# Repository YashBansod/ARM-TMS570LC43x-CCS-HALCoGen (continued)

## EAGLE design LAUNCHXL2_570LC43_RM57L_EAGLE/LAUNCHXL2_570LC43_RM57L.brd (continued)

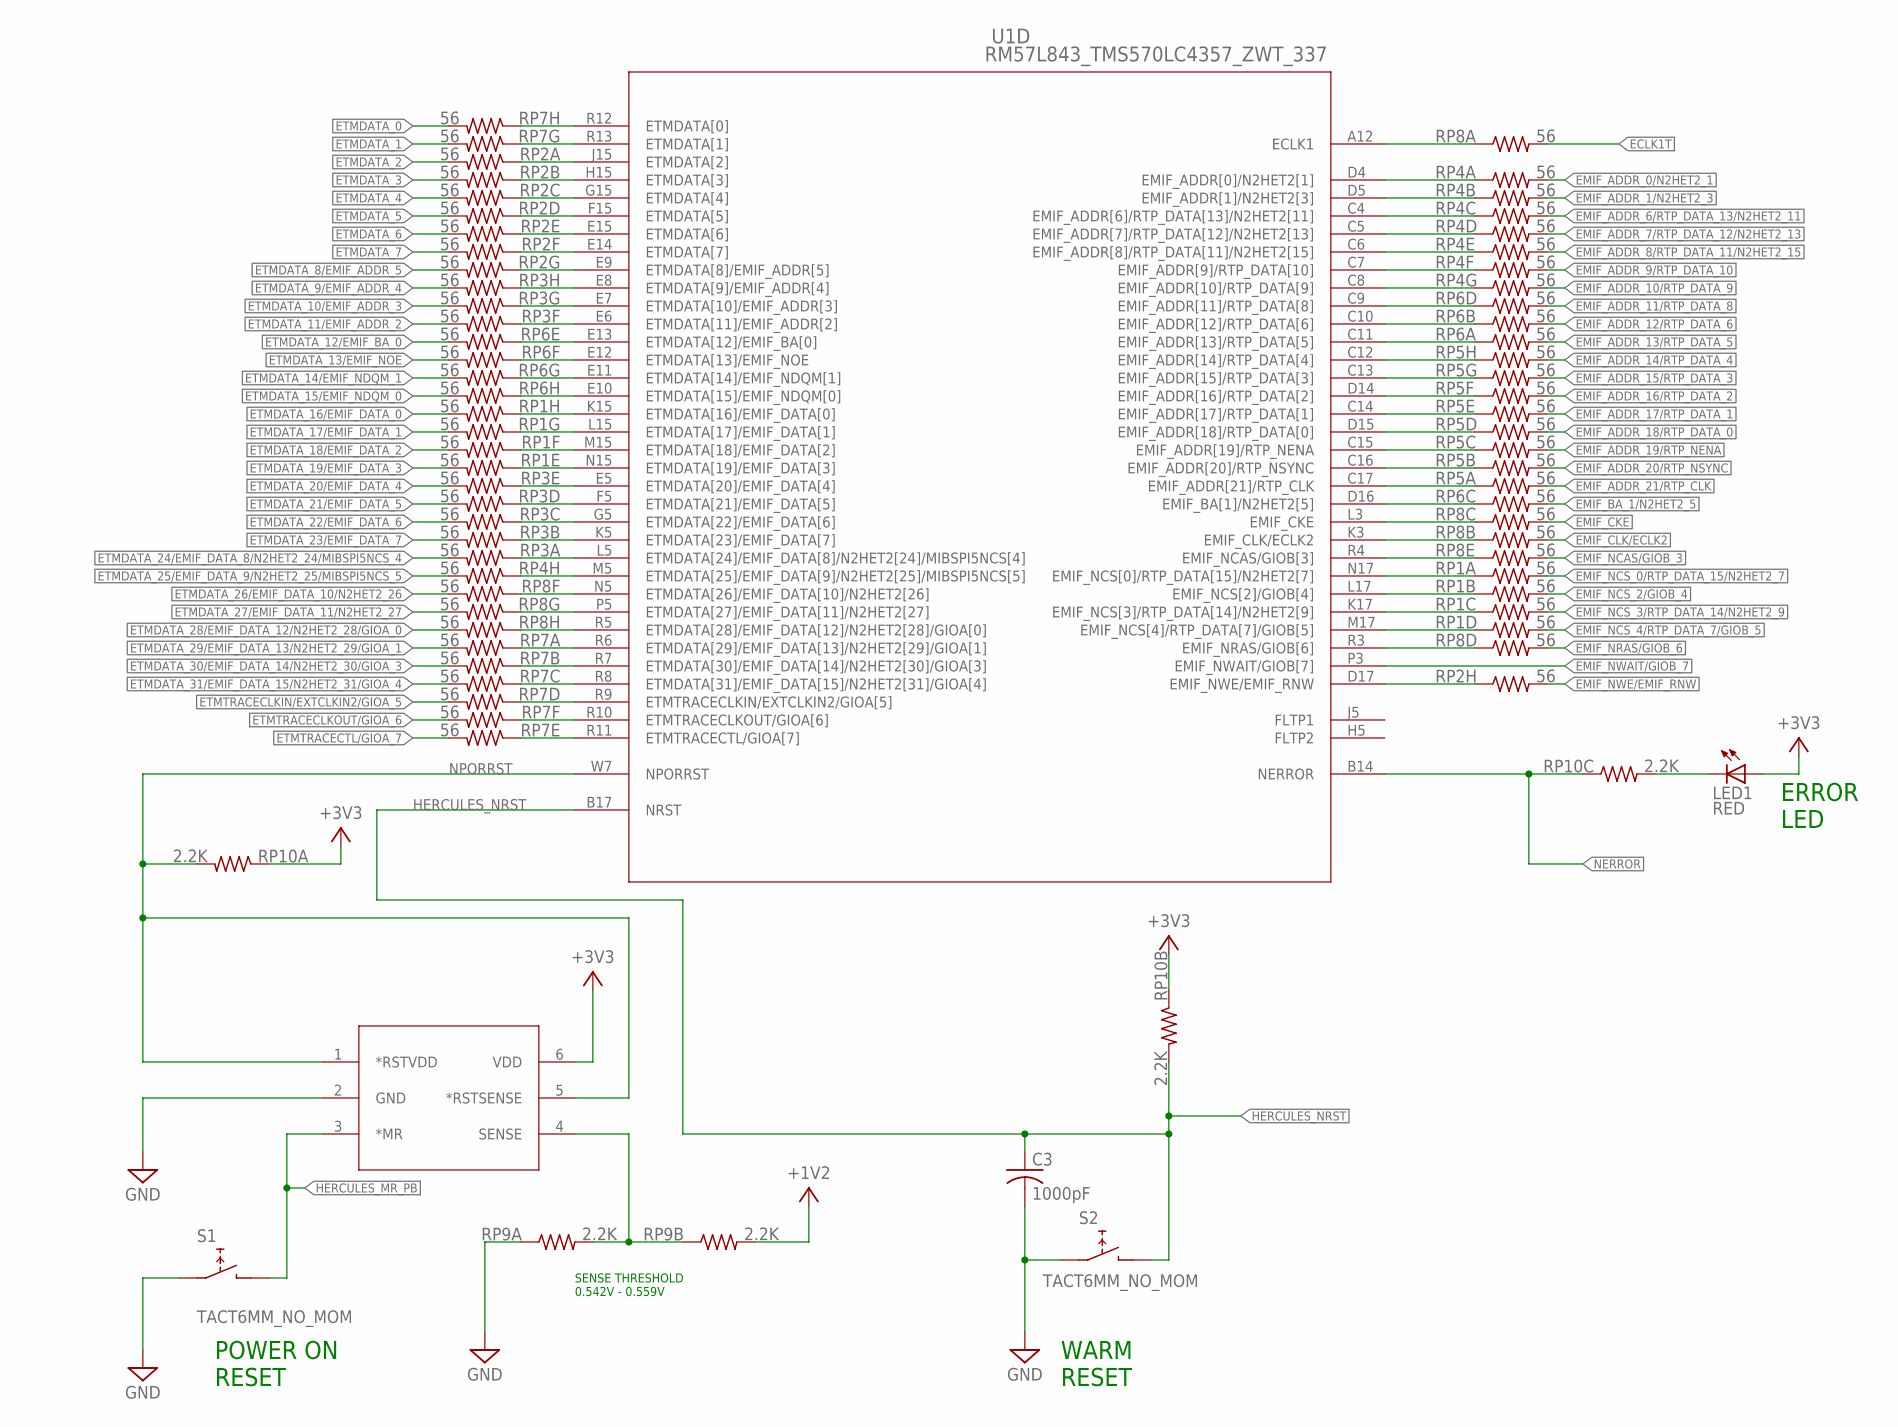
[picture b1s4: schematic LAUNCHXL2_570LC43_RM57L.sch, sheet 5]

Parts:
C3: 1000pF; C0201; PARTNO CC0201KRX7R8BB102
LED1: RED; CHIPLED_0603; PARTNO LS Q976-NR-1
RP1, RP2, RP3, RP4, RP5, RP6, RP7, RP8: 56; RP8_1506_1606; PARTNO MNR18E0APJ560
RP9, RP10: 2.2K; RP8_1506_1606; PARTNO MNR18E0APJ222
S1, S2: TACT6MM_NO_MOM; CK_PTS645_SMD; PARTNO PTS645SM43SMTR92 LFS
U1: RM57L843_TMS570LC4357_ZWT_337; ZWT337; PARTNO TMP5704357AZWTQQ1
U2: TPS3106K33_DBV_6; DBV6; PARTNO TPS3106K33DBVR

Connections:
+1V2: RP9.4 (2); also elsewhere on the board
+3V3: LED1.A, RP10.1, RP10.3 (1), U2.6 (VDD); also elsewhere on the board
ECLK1: RP8.1, U1.A12 (ECLK1)
ECLK1T: RP8.2; also elsewhere on the board
EMA0: RP4.1, U1.D4 (EMIF_ADDR[0]/N2HET2[1])
EMA1: RP4.3 (1), U1.D5 (EMIF_ADDR[1]/N2HET2[3])
EMA6: RP4.5 (1), U1.C4 (EMIF_ADDR[6]/RTP_DATA[13]/N2HET2[11])
EMA7: RP4.7 (1), U1.C5 (EMIF_ADDR[7]/RTP_DATA[12]/N2HET2[13])
EMA8: RP4.9 (1), U1.C6 (EMIF_ADDR[8]/RTP_DATA[11]/N2HET2[15])
EMA9: RP4.11 (1), U1.C7 (EMIF_ADDR[9]/RTP_DATA[10])
EMA10: RP4.13 (1), U1.C8 (EMIF_ADDR[10]/RTP_DATA[9])
EMA11: RP6.7 (1), U1.C9 (EMIF_ADDR[11]/RTP_DATA[8])
EMA12: RP6.3 (1), U1.C10 (EMIF_ADDR[12]/RTP_DATA[6])
EMA13: RP6.1, U1.C11 (EMIF_ADDR[13]/RTP_DATA[5])
EMA14: RP5.15 (1), U1.C12 (EMIF_ADDR[14]/RTP_DATA[4])
EMA15: RP5.13 (1), U1.C13 (EMIF_ADDR[15]/RTP_DATA[3])
EMA16: RP5.11 (1), U1.D14 (EMIF_ADDR[16]/RTP_DATA[2])
EMA17: RP5.9 (1), U1.C14 (EMIF_ADDR[17]/RTP_DATA[1])
EMA18: RP5.7 (1), U1.D15 (EMIF_ADDR[18]/RTP_DATA[0])
EMA19: RP5.5 (1), U1.C15 (EMIF_ADDR[19]/RTP_NENA)
EMA20: RP5.3 (1), U1.C16 (EMIF_ADDR[20]/RTP_NSYNC)
EMA21: RP5.1, U1.C17 (EMIF_ADDR[21]/RTP_CLK)
EMBA1: RP6.5 (1), U1.D16 (EMIF_BA[1]/N2HET2[5])
EMCAS: RP8.9 (1), U1.R4 (EMIF_NCAS/GIOB[3])
EMCKE: RP8.5 (1), U1.L3 (EMIF_CKE)
EMCLK: RP8.3 (1), U1.K3 (EMIF_CLK/ECLK2)
EMCS0: RP1.1, U1.N17 (EMIF_NCS[0]/RTP_DATA[15]/N2HET2[7])
EMCS2: RP1.3 (1), U1.L17 (EMIF_NCS[2]/GIOB[4])
EMCS3: RP1.5 (1), U1.K17 (EMIF_NCS[3]/RTP_DATA[14]/N2HET2[9])
EMCS4: RP1.7 (1), U1.M17 (EMIF_NCS[4]/RTP_DATA[7]/GIOB[5])
EMIF_ADDR_0/N2HET2_1: RP4.2; also elsewhere on the board
EMIF_ADDR_1/N2HET2_3: RP4.4 (2); also elsewhere on the board
EMIF_ADDR_6/RTP_DATA_13/N2HET2_11: RP4.6 (2); also elsewhere on the board
EMIF_ADDR_7/RTP_DATA_12/N2HET2_13: RP4.8 (2); also elsewhere on the board
EMIF_ADDR_8/RTP_DATA_11/N2HET2_15: RP4.10 (2); also elsewhere on the board
EMIF_ADDR_9/RTP_DATA_10: RP4.12 (2); also elsewhere on the board
EMIF_ADDR_10/RTP_DATA_9: RP4.14 (2); also elsewhere on the board
EMIF_ADDR_11/RTP_DATA_8: RP6.8 (2); also elsewhere on the board
EMIF_ADDR_12/RTP_DATA_6: RP6.4 (2); also elsewhere on the board
EMIF_ADDR_13/RTP_DATA_5: RP6.2; also elsewhere on the board
EMIF_ADDR_14/RTP_DATA_4: RP5.16 (2); also elsewhere on the board
EMIF_ADDR_15/RTP_DATA_3: RP5.14 (2); also elsewhere on the board
EMIF_ADDR_16/RTP_DATA_2: RP5.12 (2); also elsewhere on the board
EMIF_ADDR_17/RTP_DATA_1: RP5.10 (2); also elsewhere on the board
EMIF_ADDR_18/RTP_DATA_0: RP5.8 (2); also elsewhere on the board
EMIF_ADDR_19/RTP_NENA: RP5.6 (2); also elsewhere on the board
EMIF_ADDR_20/RTP_NSYNC: RP5.4 (2); also elsewhere on the board
EMIF_ADDR_21/RTP_CLK: RP5.2; also elsewhere on the board
EMIF_BA_1/N2HET2_5: RP6.6 (2); also elsewhere on the board
EMIF_CKE: RP8.6 (2); also elsewhere on the board
EMIF_CLK/ECLK2: RP8.4 (2); also elsewhere on the board
EMIF_NCAS/GIOB_3: RP8.10 (2); also elsewhere on the board
EMIF_NCS_0/RTP_DATA_15/N2HET2_7: RP1.2; also elsewhere on the board
EMIF_NCS_2/GIOB_4: RP1.4 (2); also elsewhere on the board
EMIF_NCS_3/RTP_DATA_14/N2HET2_9: RP1.6 (2); also elsewhere on the board
EMIF_NCS_4/RTP_DATA_7/GIOB_5: RP1.8 (2); also elsewhere on the board
EMIF_NRAS/GIOB_6: RP8.8 (2); also elsewhere on the board
EMIF_NWAIT/GIOB_7: U1.P3 (EMIF_NWAIT/GIOB[7]); also elsewhere on the board
EMIF_NWE/EMIF_RNW: RP2.16 (2); also elsewhere on the board
EMRAS: RP8.7 (1), U1.R3 (EMIF_NRAS/GIOB[6])
EMWE: RP2.15 (1), U1.D17 (EMIF_NWE/EMIF_RNW)
ETD0: RP7.15 (1), U1.R12 (ETMDATA[0])
ETD1: RP7.13 (1), U1.R13 (ETMDATA[1])
ETD2: RP2.1, U1.J15 (ETMDATA[2])
ETD3: RP2.3 (1), U1.H15 (ETMDATA[3])
ETD4: RP2.5 (1), U1.G15 (ETMDATA[4])
ETD5: RP2.7 (1), U1.F15 (ETMDATA[5])
ETD6: RP2.9 (1), U1.E15 (ETMDATA[6])
ETD7: RP2.11 (1), U1.E14 (ETMDATA[7])
ETD8: RP2.13 (1), U1.E9 (ETMDATA[8]/EMIF_ADDR[5])
ETD9: RP3.15 (1), U1.E8 (ETMDATA[9]/EMIF_ADDR[4])
ETD10: RP3.13 (1), U1.E7 (ETMDATA[10]/EMIF_ADDR[3])
ETD11: RP3.11 (1), U1.E6 (ETMDATA[11]/EMIF_ADDR[2])
ETD12: RP6.9 (1), U1.E13 (ETMDATA[12]/EMIF_BA[0])
ETD13: RP6.11 (1), U1.E12 (ETMDATA[13]/EMIF_NOE)
ETD14: RP6.13 (1), U1.E11 (ETMDATA[14]/EMIF_NDQM[1])
ETD15: RP6.15 (1), U1.E10 (ETMDATA[15]/EMIF_NDQM[0])
ETD16: RP1.15 (1), U1.K15 (ETMDATA[16]/EMIF_DATA[0])
ETD17: RP1.13 (1), U1.L15 (ETMDATA[17]/EMIF_DATA[1])
ETD18: RP1.11 (1), U1.M15 (ETMDATA[18]/EMIF_DATA[2])
ETD19: RP1.9 (1), U1.N15 (ETMDATA[19]/EMIF_DATA[3])
ETD20: RP3.9 (1), U1.E5 (ETMDATA[20]/EMIF_DATA[4])
ETD21: RP3.7 (1), U1.F5 (ETMDATA[21]/EMIF_DATA[5])
ETD22: RP3.5 (1), U1.G5 (ETMDATA[22]/EMIF_DATA[6])
ETD23: RP3.3 (1), U1.K5 (ETMDATA[23]/EMIF_DATA[7])
ETD24: RP3.1, U1.L5 (ETMDATA[24]/EMIF_DATA[8]/N2HET2[24]/MIB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)
ETD25: RP4.15 (1), U1.M5 (ETMDATA[25]/EMIF_DATA[9]/N2HET2[25]/MIB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)
ETD26: RP8.11 (1), U1.N5 (ETMDATA[26]/EMIF_DATA[10]/N2HET2[26])
ETD27: RP8.13 (1), U1.P5 (ETMDATA[27]/EMIF_DATA[11]/N2HET2[27])
ETD28: RP8.15 (1), U1.R5 (ETMDATA[28]/EMIF_DATA[12]/N2HET2[28]/GI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)
ETD29: RP7.1, U1.R6 (ETMDATA[29]/EMIF_DATA[13]/N2HET2[29]/GI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)
ETD30: RP7.3 (1), U1.R7 (ETMDATA[30]/EMIF_DATA[14]/N2HET2[30]/GI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)
ETD31: RP7.5 (1), U1.R8 (ETMDATA[31]/EMIF_DATA[15]/N2HET2[31]/GI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)
ETD32: RP7.7 (1), U1.R9 (ETMTRACECLKIN/EXTCLKIN2/GIOA[5])
ETD33: RP7.11 (1), U1.R10 (ETMTRACECLKOUT/GIOA[6])
ETD34: RP7.9 (1), U1.R11 (ETMTRACECTL/GIOA[7])
ETMDATA_0: RP7.16 (2); also elsewhere on the board
ETMDATA_1: RP7.14 (2); also elsewhere on the board
ETMDATA_2: RP2.2; also elsewhere on the board
ETMDATA_3: RP2.4 (2); also elsewhere on the board
ETMDATA_4: RP2.6 (2); also elsewhere on the board
ETMDATA_5: RP2.8 (2); also elsewhere on the board
ETMDATA_6: RP2.10 (2); also elsewhere on the board
ETMDATA_7: RP2.12 (2); also elsewhere on the board
ETMDATA_8/EMIF_ADDR_5: RP2.14 (2); also elsewhere on the board
ETMDATA_9/EMIF_ADDR_4: RP3.16 (2); also elsewhere on the board
ETMDATA_10/EMIF_ADDR_3: RP3.14 (2); also elsewhere on the board
ETMDATA_11/EMIF_ADDR_2: RP3.12 (2); also elsewhere on the board
ETMDATA_12/EMIF_BA_0: RP6.10 (2); also elsewhere on the board
ETMDATA_13/EMIF_NOE: RP6.12 (2); also elsewhere on the board
ETMDATA_14/EMIF_NDQM_1: RP6.14 (2); also elsewhere on the board
ETMDATA_15/EMIF_NDQM_0: RP6.16 (2); also elsewhere on the board
ETMDATA_16/EMIF_DATA_0: RP1.16 (2); also elsewhere on the board
ETMDATA_17/EMIF_DATA_1: RP1.14 (2); also elsewhere on the board
ETMDATA_18/EMIF_DATA_2: RP1.12 (2); also elsewhere on the board
ETMDATA_19/EMIF_DATA_3: RP1.10 (2); also elsewhere on the board
ETMDATA_20/EMIF_DATA_4: RP3.10 (2); also elsewhere on the board
ETMDATA_21/EMIF_DATA_5: RP3.8 (2); also elsewhere on the board
ETMDATA_22/EMIF_DATA_6: RP3.6 (2); also elsewhere on the board
ETMDATA_23/EMIF_DATA_7: RP3.4 (2); also elsewhere on the board
ETMDATA_24/EMIF_DATA_8/N2HET2_24/MIBSPI5NCS_4: RP3.2; also elsewhere on the board
ETMDATA_25/EMIF_DATA_9/N2HET2_25/MIBSPI5NCS_5: RP4.16 (2); also elsewhere on the board
ETMDATA_26/EMIF_DATA_10/N2HET2_26: RP8.12 (2); also elsewhere on the board
ETMDATA_27/EMIF_DATA_11/N2HET2_27: RP8.14 (2); also elsewhere on the board
ETMDATA_28/EMIF_DATA_12/N2HET2_28/GIOA_0: RP8.16 (2); also elsewhere on the board
ETMDATA_29/EMIF_DATA_13/N2HET2_29/GIOA_1: RP7.2; also elsewhere on the board
ETMDATA_30/EMIF_DATA_14/N2HET2_30/GIOA_3: RP7.4 (2); also elsewhere on the board
ETMDATA_31/EMIF_DATA_15/N2HET2_31/GIOA_4: RP7.6 (2); also elsewhere on the board
ETMTRACECLKIN/EXTCLKIN2/GIOA_5: RP7.8 (2); also elsewhere on the board
ETMTRACECLKOUT/GIOA_6: RP7.12 (2); also elsewhere on the board
ETMTRACECTL/GIOA_7: RP7.10 (2); also elsewhere on the board
GND: C3.2, RP9.1, S1.1 (12), S1.2 (12), S2.1 (12), S2.2 (12), U2.2 (GND); also elsewhere on the board
HERCULES_MR_PB: S1.3 (34), S1.4 (34), U2.3 (*MR); also elsewhere on the board
HERCULES_NRST: C3.1, RP10.4 (2), S2.3 (34), S2.4 (34), U1.B17 (NRST); also elsewhere on the board
unnamed: LED1.C, RP10.6 (2)
NERROR: RP10.5 (1), U1.B14 (NERROR); also elsewhere on the board
NPORRST: RP10.2, U1.W7 (NPORRST), U2.1 (*RSTVDD), U2.5 (*RSTSENSE)
SENSE: RP9.2, RP9.3 (1), U2.4 (SENSE)

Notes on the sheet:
SENSE THRESHOLD 0.542V - 0.559V
POWER ON RESET
WARM RESET
ERROR LED

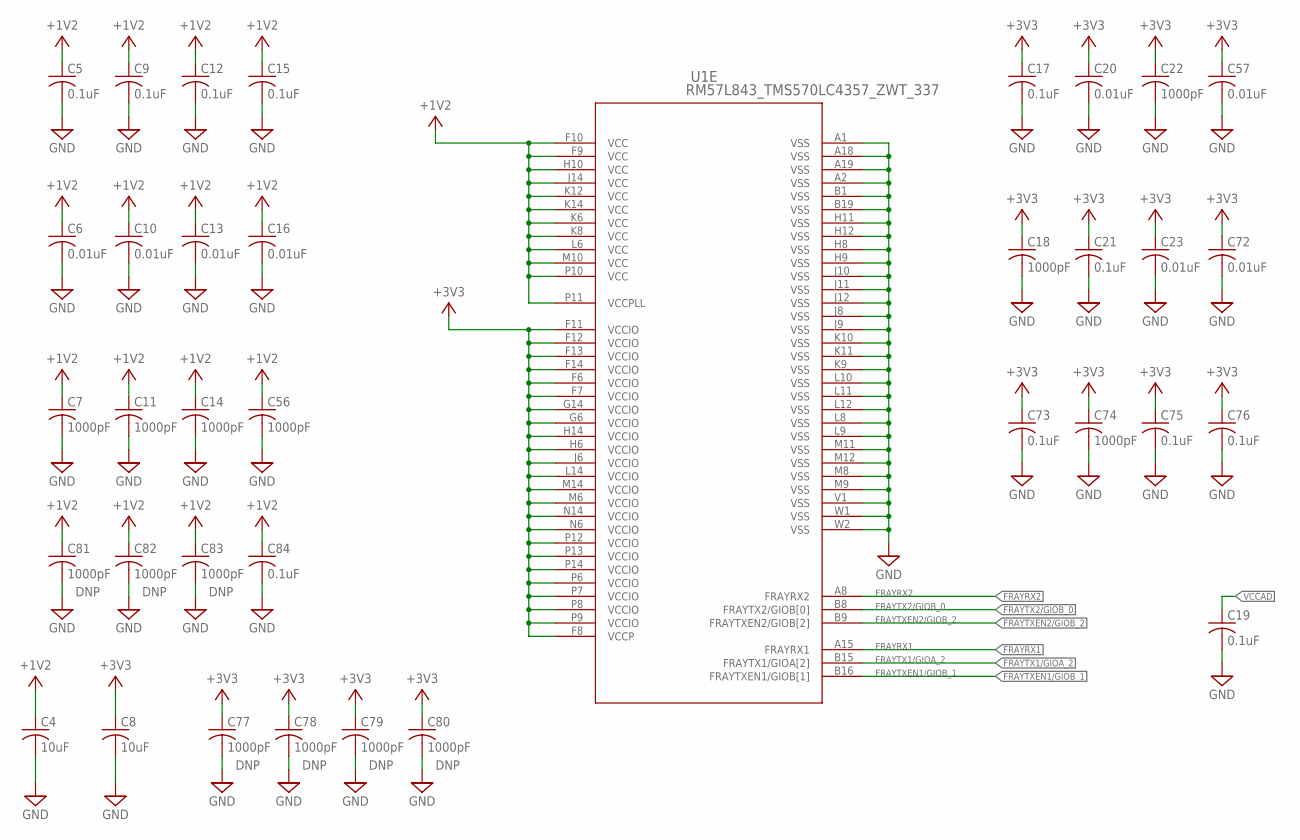
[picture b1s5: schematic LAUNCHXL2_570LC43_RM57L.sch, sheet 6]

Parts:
C4, C8: 10uF; C0805K; PARTNO C0805C106K8PACTU
C5, C9, C12, C15, C17, C19, C21, C73, C75, C76, C84: 0.1uF; C0201; PARTNO CL03A104MQ3NNNC
C6, C10, C13, C16, C20, C23, C57, C72: 0.01uF; C0201; PARTNO CL03A103KQ3NNNC
C7, C11, C14, C18, C22, C56, C74, C77, C78, C79, C80, C81, C82, C83: 1000pF; C0201; PARTNO CC0201KRX7R8BB102
U1: RM57L843_TMS570LC4357_ZWT_337; ZWT337; PARTNO TMP5704357AZWTQQ1

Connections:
+1V2: C4.1, C5.1, C6.1, C7.1, C9.1, C10.1, C11.1, C12.1, C13.1, C14.1, C15.1, C16.1, C56.1, C81.1, C82.1, C83.1, C84.1, U1.F9 (VCC), U1.F10 (VCC), U1.H10 (VCC), U1.J14 (VCC), U1.K6 (VCC), U1.K8 (VCC), U1.K12 (VCC), U1.K14 (VCC), U1.L6 (VCC), U1.M10 (VCC), U1.P10 (VCC), U1.P11 (VCCPLL); also elsewhere on the board
+3V3: C8.1, C17.1, C18.1, C20.1, C21.1, C22.1, C23.1, C57.1, C72.1, C73.1, C74.1, C75.1, C76.1, C77.1, C78.1, C79.1, C80.1, U1.F6 (VCCIO), U1.F7 (VCCIO), U1.F8 (VCCP), U1.F11 (VCCIO), U1.F12 (VCCIO), U1.F13 (VCCIO), U1.F14 (VCCIO), U1.G6 (VCCIO), U1.G14 (VCCIO), U1.H6 (VCCIO), U1.H14 (VCCIO), U1.J6 (VCCIO), U1.L14 (VCCIO), U1.M6 (VCCIO), U1.M14 (VCCIO), U1.N6 (VCCIO), U1.N14 (VCCIO), U1.P6 (VCCIO), U1.P7 (VCCIO), U1.P8 (VCCIO), U1.P9 (VCCIO), U1.P12 (VCCIO), U1.P13 (VCCIO), U1.P14 (VCCIO); also elsewhere on the board
FRAYRX1: U1.A15 (FRAYRX1); also elsewhere on the board
FRAYRX2: U1.A8 (FRAYRX2); also elsewhere on the board
FRAYTX1/GIOA_2: U1.B15 (FRAYTX1/GIOA[2]); also elsewhere on the board
FRAYTX2/GIOB_0: U1.B8 (FRAYTX2/GIOB[0]); also elsewhere on the board
FRAYTXEN1/GIOB_1: U1.B16 (FRAYTXEN1/GIOB[1]); also elsewhere on the board
FRAYTXEN2/GIOB_2: U1.B9 (FRAYTXEN2/GIOB[2]); also elsewhere on the board
GND: C4.2, C5.2, C6.2, C7.2, C8.2, C9.2, C10.2, C11.2, C12.2, C13.2, C14.2, C15.2, C16.2, C17.2, C18.2, C19.2, C20.2, C21.2, C22.2, C23.2, C56.2, C57.2, C72.2, C73.2, C74.2, C75.2, C76.2, C77.2, C78.2, C79.2, C80.2, C81.2, C82.2, C83.2, C84.2, U1.A1 (VSS), U1.A2 (VSS), U1.A18 (VSS), U1.A19 (VSS), U1.B1 (VSS), U1.B19 (VSS), U1.H8 (VSS), U1.H9 (VSS), U1.H11 (VSS), U1.H12 (VSS), U1.J8 (VSS), U1.J9 (VSS), U1.J10 (VSS), U1.J11 (VSS), U1.J12 (VSS), U1.K9 (VSS), U1.K10 (VSS), U1.K11 (VSS), U1.L8 (VSS), U1.L9 (VSS), U1.L10 (VSS), U1.L11 (VSS), U1.L12 (VSS), U1.M8 (VSS), U1.M9 (VSS), U1.M11 (VSS), U1.M12 (VSS), U1.V1 (VSS), U1.W1 (VSS), U1.W2 (VSS); also elsewhere on the board
VCCAD: C19.1; also elsewhere on the board

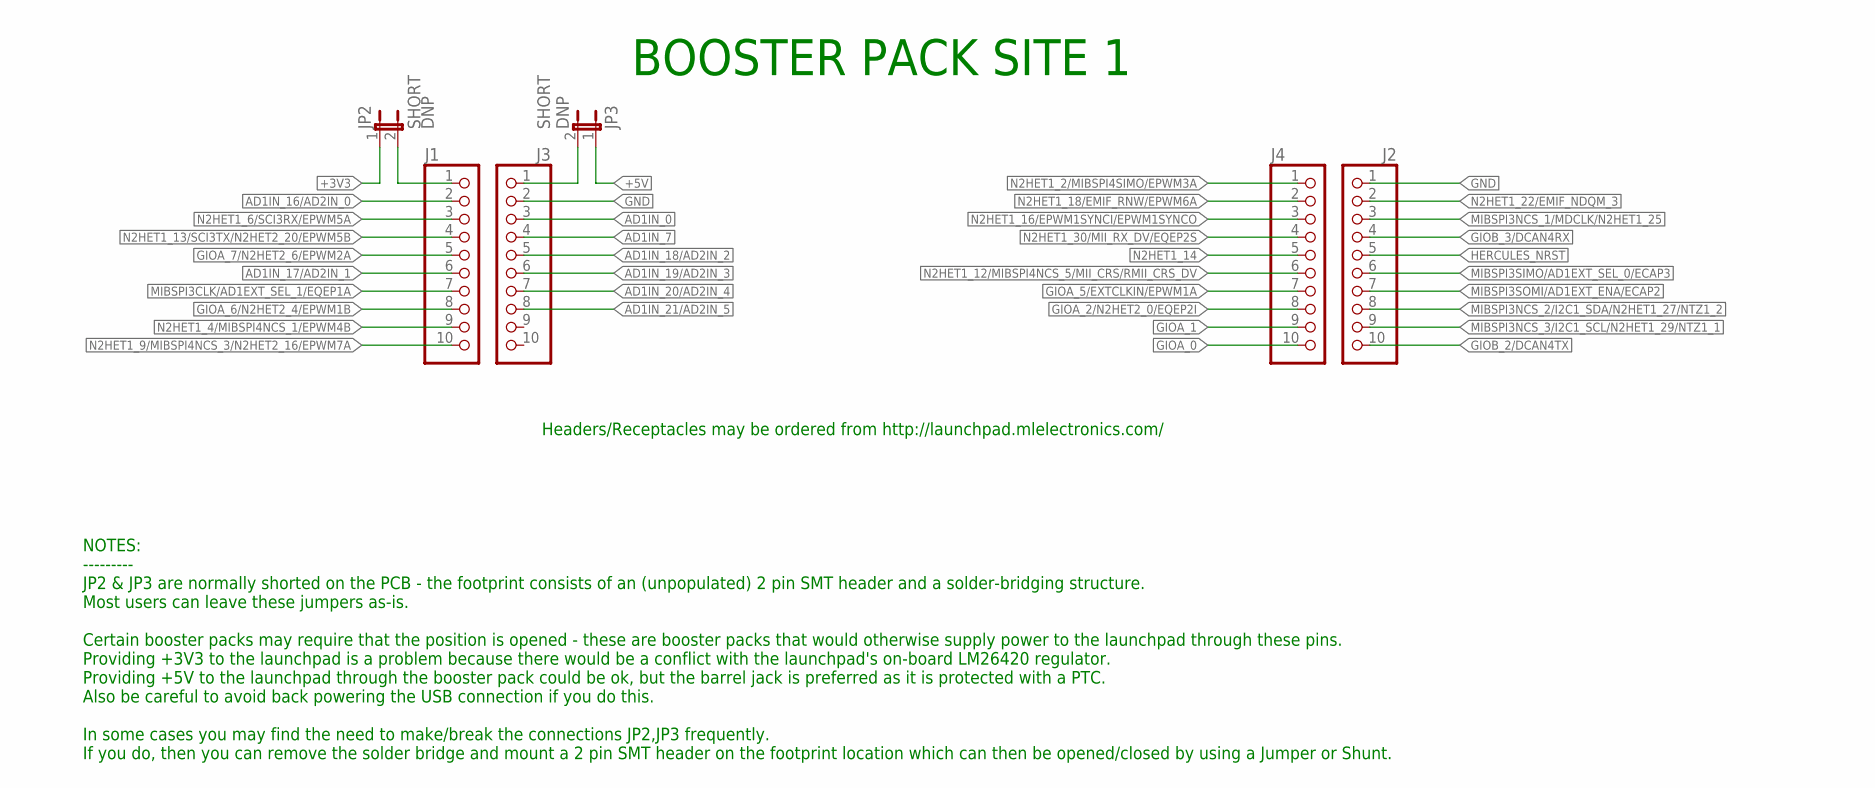
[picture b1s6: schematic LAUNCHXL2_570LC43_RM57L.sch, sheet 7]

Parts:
J1, J2, J3, J4: PINHD-1X10; 1X10; PARTNO CRD-081413-A-F
JP2, JP3: SHORT; JP1_SHORT; PARTNO GEC02DABN-M30

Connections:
+3V3: JP2.1; also elsewhere on the board
+5V: JP3.1; also elsewhere on the board
AD1IN_0: J3.3; also elsewhere on the board
AD1IN_7: J3.4; also elsewhere on the board
AD1IN_16/AD2IN_0: J1.2; also elsewhere on the board
AD1IN_17/AD2IN_1: J1.6; also elsewhere on the board
AD1IN_18/AD2IN_2: J3.5; also elsewhere on the board
AD1IN_19/AD2IN_3: J3.6; also elsewhere on the board
AD1IN_20/AD2IN_4: J3.7; also elsewhere on the board
AD1IN_21/AD2IN_5: J3.8; also elsewhere on the board
GIOA_0: J4.10; also elsewhere on the board
GIOA_1: J4.9; also elsewhere on the board
GIOA_2/N2HET2_0/EQEP2I: J4.8; also elsewhere on the board
GIOA_5/EXTCLKIN/EPWM1A: J4.7; also elsewhere on the board
GIOA_6/N2HET2_4/EPWM1B: J1.8; also elsewhere on the board
GIOA_7/N2HET2_6/EPWM2A: J1.5; also elsewhere on the board
GIOB_2/DCAN4TX: J2.10; also elsewhere on the board
GIOB_3/DCAN4RX: J2.4; also elsewhere on the board
GND: J2.1, J3.2; also elsewhere on the board
HERCULES_NRST: J2.5; also elsewhere on the board
MIBSPI3CLK/AD1EXT_SEL_1/EQEP1A: J1.7; also elsewhere on the board
MIBSPI3NCS_1/MDCLK/N2HET1_25: J2.3; also elsewhere on the board
MIBSPI3NCS_2/I2C1_SDA/N2HET1_27/NTZ1_2: J2.8; also elsewhere on the board
MIBSPI3NCS_3/I2C1_SCL/N2HET1_29/NTZ1_1: J2.9; also elsewhere on the board
MIBSPI3SIMO/AD1EXT_SEL_0/ECAP3: J2.6; also elsewhere on the board
MIBSPI3SOMI/AD1EXT_ENA/ECAP2: J2.7; also elsewhere on the board
N2HET1_2/MIBSPI4SIMO/EPWM3A: J4.1; also elsewhere on the board
N2HET1_4/MIBSPI4NCS_1/EPWM4B: J1.9; also elsewhere on the board
N2HET1_6/SCI3RX/EPWM5A: J1.3; also elsewhere on the board
N2HET1_9/MIBSPI4NCS_3/N2HET2_16/EPWM7A: J1.10; also elsewhere on the board
N2HET1_12/MIBSPI4NCS_5/MII_CRS/RMII_CRS_DV: J4.6; also elsewhere on the board
N2HET1_13/SCI3TX/N2HET2_20/EPWM5B: J1.4; also elsewhere on the board
N2HET1_14: J4.5; also elsewhere on the board
N2HET1_16/EPWM1SYNCI/EPWM1SYNCO: J4.3; also elsewhere on the board
N2HET1_18/EMIF_RNW/EPWM6A: J4.2; also elsewhere on the board
N2HET1_22/EMIF_NDQM_3: J2.2; also elsewhere on the board
N2HET1_30/MII_RX_DV/EQEP2S: J4.4; also elsewhere on the board
unnamed: J1.1, JP2.2
unnamed: J3.1, JP3.2

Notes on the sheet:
BOOSTER PACK SITE 1
NOTES: --------- JP2 & JP3 are normally shorted on the PCB - the footprint consists of an (unpopulated) 2 pin SMT header and a solder-bridging structure. Most users can leave these jumpers as-is. Certain booster packs may require that the position is opened - these are booster packs that would othe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
Headers/Receptacles may be ordered from http://launchpad.mlelectronics.com/

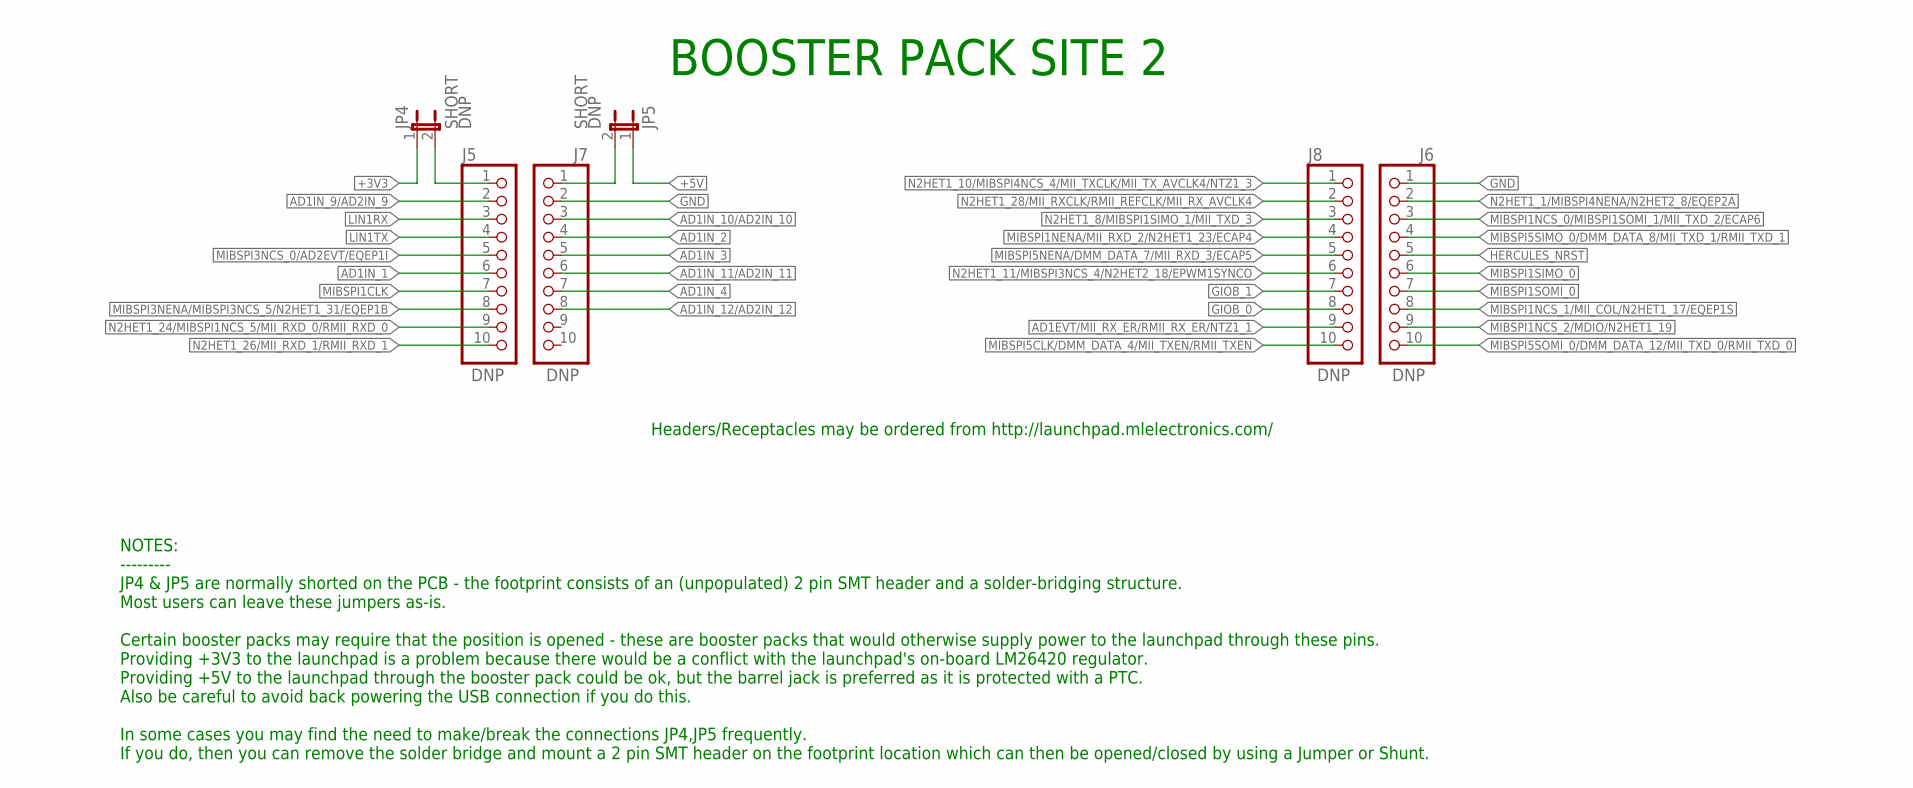
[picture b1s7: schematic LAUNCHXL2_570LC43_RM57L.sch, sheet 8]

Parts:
J5, J6, J7, J8: PINHD-1X10; 1X10; PARTNO CRD-081413-A-F
JP4, JP5: SHORT; JP1_SHORT; PARTNO GEC02DABN-M30

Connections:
+3V3: JP4.1; also elsewhere on the board
+5V: JP5.1; also elsewhere on the board
AD1EVT/MII_RX_ER/RMII_RX_ER/NTZ1_1: J8.9; also elsewhere on the board
AD1IN_1: J5.6; also elsewhere on the board
AD1IN_2: J7.4; also elsewhere on the board
AD1IN_3: J7.5; also elsewhere on the board
AD1IN_4: J7.7; also elsewhere on the board
AD1IN_9/AD2IN_9: J5.2; also elsewhere on the board
AD1IN_10/AD2IN_10: J7.3; also elsewhere on the board
AD1IN_11/AD2IN_11: J7.6; also elsewhere on the board
AD1IN_12/AD2IN_12: J7.8; also elsewhere on the board
GIOB_0: J8.8; also elsewhere on the board
GIOB_1: J8.7; also elsewhere on the board
GND: J6.1, J7.2; also elsewhere on the board
HERCULES_NRST: J6.5; also elsewhere on the board
LIN1RX: J5.3; also elsewhere on the board
LIN1TX: J5.4; also elsewhere on the board
MIBSPI1CLK: J5.7; also elsewhere on the board
MIBSPI1NCS_0/MIBSPI1SOMI_1/MII_TXD_2/ECAP6: J6.3; also elsewhere on the board
MIBSPI1NCS_1/MII_COL/N2HET1_17/EQEP1S: J6.8; also elsewhere on the board
MIBSPI1NCS_2/MDIO/N2HET1_19: J6.9; also elsewhere on the board
MIBSPI1NENA/MII_RXD_2/N2HET1_23/ECAP4: J8.4; also elsewhere on the board
MIBSPI1SIMO_0: J6.6; also elsewhere on the board
MIBSPI1SOMI_0: J6.7; also elsewhere on the board
MIBSPI3NCS_0/AD2EVT/EQEP1I: J5.5; also elsewhere on the board
MIBSPI3NENA/MIBSPI3NCS_5/N2HET1_31/EQEP1B: J5.8; also elsewhere on the board
MIBSPI5CLK/DMM_DATA_4/MII_TXEN/RMII_TXEN: J8.10; also elsewhere on the board
MIBSPI5NENA/DMM_DATA_7/MII_RXD_3/ECAP5: J8.5; also elsewhere on the board
MIBSPI5SIMO_0/DMM_DATA_8/MII_TXD_1/RMII_TXD_1: J6.4; also elsewhere on the board
MIBSPI5SOMI_0/DMM_DATA_12/MII_TXD_0/RMII_TXD_0: J6.10; also elsewhere on the board
N2HET1_1/MIBSPI4NENA/N2HET2_8/EQEP2A: J6.2; also elsewhere on the board
N2HET1_8/MIBSPI1SIMO_1/MII_TXD_3: J8.3; also elsewhere on the board
N2HET1_10/MIBSPI4NCS_4/MII_TXCLK/MII_TX_AVCLK4/NTZ1_3: J8.1; also elsewhere on the board
N2HET1_11/MIBSPI3NCS_4/N2HET2_18/EPWM1SYNCO: J8.6; also elsewhere on the board
N2HET1_24/MIBSPI1NCS_5/MII_RXD_0/RMII_RXD_0: J5.9; also elsewhere on the board
N2HET1_26/MII_RXD_1/RMII_RXD_1: J5.10; also elsewhere on the board
N2HET1_28/MII_RXCLK/RMII_REFCLK/MII_RX_AVCLK4: J8.2; also elsewhere on the board
unnamed: J5.1, JP4.2
unnamed: J7.1, JP5.2

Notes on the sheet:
BOOSTER PACK SITE 2
NOTES: --------- JP4 & JP5 are normally shorted on the PCB - the footprint consists of an (unpopulated) 2 pin SMT header and a solder-bridging structure. Most users can leave these jumpers as-is. Certain booster packs may require that the position is opened - these are booster packs that would othe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
Headers/Receptacles may be ordered from http://launchpad.mlelectronics.com/

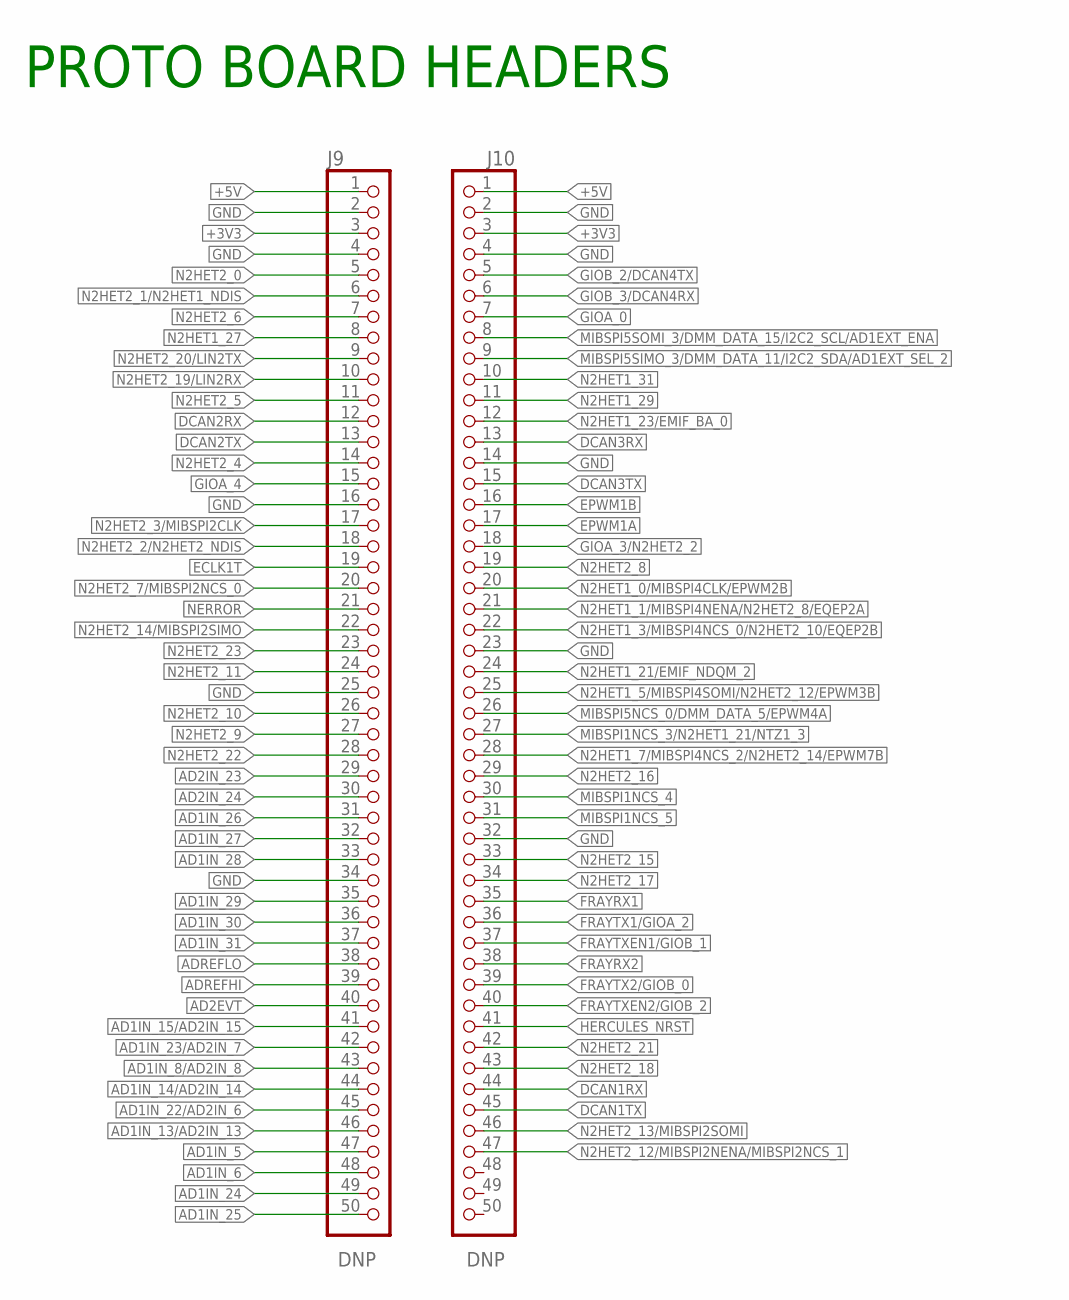
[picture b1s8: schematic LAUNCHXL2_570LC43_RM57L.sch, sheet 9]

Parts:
J9: PINHD-1X50ALT; 1X50_ALT; PARTNO TSW-150-07-T-S
J10: PINHD-1X50; 1X50; PARTNO TSW-150-07-T-S

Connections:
+3V3: J9.3, J10.3; also elsewhere on the board
+5V: J9.1, J10.1; also elsewhere on the board
AD1IN_5: J9.47; also elsewhere on the board
AD1IN_6: J9.48; also elsewhere on the board
AD1IN_8/AD2IN_8: J9.43; also elsewhere on the board
AD1IN_13/AD2IN_13: J9.46; also elsewhere on the board
AD1IN_14/AD2IN_14: J9.44; also elsewhere on the board
AD1IN_15/AD2IN_15: J9.41; also elsewhere on the board
AD1IN_22/AD2IN_6: J9.45; also elsewhere on the board
AD1IN_23/AD2IN_7: J9.42; also elsewhere on the board
AD1IN_24: J9.49; also elsewhere on the board
AD1IN_25: J9.50; also elsewhere on the board
AD1IN_26: J9.31; also elsewhere on the board
AD1IN_27: J9.32; also elsewhere on the board
AD1IN_28: J9.33; also elsewhere on the board
AD1IN_29: J9.35; also elsewhere on the board
AD1IN_30: J9.36; also elsewhere on the board
AD1IN_31: J9.37; also elsewhere on the board
AD2EVT: J9.40; also elsewhere on the board
AD2IN_23: J9.29; also elsewhere on the board
AD2IN_24: J9.30; also elsewhere on the board
ADREFHI: J9.39; also elsewhere on the board
ADREFLO: J9.38; also elsewhere on the board
DCAN1RX: J10.44; also elsewhere on the board
DCAN1TX: J10.45; also elsewhere on the board
DCAN2RX: J9.12; also elsewhere on the board
DCAN2TX: J9.13; also elsewhere on the board
DCAN3RX: J10.13; also elsewhere on the board
DCAN3TX: J10.15; also elsewhere on the board
ECLK1T: J9.19; also elsewhere on the board
EPWM1A: J10.17; also elsewhere on the board
EPWM1B: J10.16; also elsewhere on the board
FRAYRX1: J10.35; also elsewhere on the board
FRAYRX2: J10.38; also elsewhere on the board
FRAYTX1/GIOA_2: J10.36; also elsewhere on the board
FRAYTX2/GIOB_0: J10.39; also elsewhere on the board
FRAYTXEN1/GIOB_1: J10.37; also elsewhere on the board
FRAYTXEN2/GIOB_2: J10.40; also elsewhere on the board
GIOA_0: J10.7; also elsewhere on the board
GIOA_3/N2HET2_2: J10.18; also elsewhere on the board
GIOA_4: J9.15; also elsewhere on the board
GIOB_2/DCAN4TX: J10.5; also elsewhere on the board
GIOB_3/DCAN4RX: J10.6; also elsewhere on the board
GND: J9.2, J9.4, J9.16, J9.25, J9.34, J10.2, J10.4, J10.14, J10.23, J10.32; also elsewhere on the board
HERCULES_NRST: J10.41; also elsewhere on the board
MIBSPI1NCS_3/N2HET1_21/NTZ1_3: J10.27; also elsewhere on the board
MIBSPI1NCS_4: J10.30; also elsewhere on the board
MIBSPI1NCS_5: J10.31; also elsewhere on the board
MIBSPI5NCS_0/DMM_DATA_5/EPWM4A: J10.26; also elsewhere on the board
MIBSPI5SIMO_3/DMM_DATA_11/I2C2_SDA/AD1EXT_SEL_2: J10.9; also elsewhere on the board
MIBSPI5SOMI_3/DMM_DATA_15/I2C2_SCL/AD1EXT_ENA: J10.8; also elsewhere on the board
N2HET1_0/MIBSPI4CLK/EPWM2B: J10.20; also elsewhere on the board
N2HET1_1/MIBSPI4NENA/N2HET2_8/EQEP2A: J10.21; also elsewhere on the board
N2HET1_3/MIBSPI4NCS_0/N2HET2_10/EQEP2B: J10.22; also elsewhere on the board
N2HET1_5/MIBSPI4SOMI/N2HET2_12/EPWM3B: J10.25; also elsewhere on the board
N2HET1_7/MIBSPI4NCS_2/N2HET2_14/EPWM7B: J10.28; also elsewhere on the board
N2HET1_21/EMIF_NDQM_2: J10.24; also elsewhere on the board
N2HET1_23/EMIF_BA_0: J10.12; also elsewhere on the board
N2HET1_27: J9.8; also elsewhere on the board
N2HET1_29: J10.11; also elsewhere on the board
N2HET1_31: J10.10; also elsewhere on the board
N2HET2_0: J9.5; also elsewhere on the board
N2HET2_1/N2HET1_NDIS: J9.6; also elsewhere on the board
N2HET2_2/N2HET2_NDIS: J9.18; also elsewhere on the board
N2HET2_3/MIBSPI2CLK: J9.17; also elsewhere on the board
N2HET2_4: J9.14; also elsewhere on the board
N2HET2_5: J9.11; also elsewhere on the board
N2HET2_6: J9.7; also elsewhere on the board
N2HET2_7/MIBSPI2NCS_0: J9.20; also elsewhere on the board
N2HET2_8: J10.19; also elsewhere on the board
N2HET2_9: J9.27; also elsewhere on the board
N2HET2_10: J9.26; also elsewhere on the board
N2HET2_11: J9.24; also elsewhere on the board
N2HET2_12/MIBSPI2NENA/MIBSPI2NCS_1: J10.47; also elsewhere on the board
N2HET2_13/MIBSPI2SOMI: J10.46; also elsewhere on the board
N2HET2_14/MIBSPI2SIMO: J9.22; also elsewhere on the board
N2HET2_15: J10.33; also elsewhere on the board
N2HET2_16: J10.29; also elsewhere on the board
N2HET2_17: J10.34; also elsewhere on the board
N2HET2_18: J10.43; also elsewhere on the board
N2HET2_19/LIN2RX: J9.10; also elsewhere on the board
N2HET2_20/LIN2TX: J9.9; also elsewhere on the board
N2HET2_21: J10.42; also elsewhere on the board
N2HET2_22: J9.28; also elsewhere on the board
N2HET2_23: J9.23; also elsewhere on the board
NERROR: J9.21; also elsewhere on the board

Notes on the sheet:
PROTO BOARD HEADERS

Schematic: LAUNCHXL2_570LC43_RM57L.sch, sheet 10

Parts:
C24: 4700pF; C0201; PARTNO GRM033R71A472KA01D
LED2, LED3: GRN; CHIPLED_0603; PARTNO QBLP601-AG
RP9: 2.2K; RP8_1506_1606; PARTNO MNR18E0APJ222
S3, S4: TACT6MM_NO_MOM; CK_PTS645_SMD; PARTNO PTS645SM43SMTR92 LFS
U10: 1K; SOT23; PARTNO PVZ2A102C04B00

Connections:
+3V3: RP9.9 (1), RP9.11 (1), U10.1; also elsewhere on the board
AD1IN_6: C24.1, U10.3; also elsewhere on the board
GIOB_4: RP9.10 (2), S3.3 (34), S3.4 (34); also elsewhere on the board
GIOB_5: RP9.12 (2), S4.3 (34), S4.4 (34); also elsewhere on the board
GIOB_6/NERROR1: LED2.A; also elsewhere on the board
GIOB_7/NERROR2/NTZ1_2: LED3.A; also elsewhere on the board
GND: C24.2, RP9.5 (1), RP9.8 (2), S3.1 (12), S3.2 (12), S4.1 (12), S4.2 (12), U10.2; also elsewhere on the board
RP9C: LED2.C, RP9.6 (2)
RP9D: LED3.C, RP9.7 (1)

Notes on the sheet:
USER
TRIM POT. FOR ANALOG INPUT (REPLACES TEMP SENSOR)

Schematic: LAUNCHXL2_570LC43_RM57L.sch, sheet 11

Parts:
+1V2: DNP; 1,6/0,9; PARTNO BOM_EXCLUDE
C25, C27, C30, C32, C33: 22uF; C0805K; PARTNO CL21A226MQQNNNE
C28: 1uF; C0402K; PARTNO GRM155R60J105KE19D
C29: 0.1uF; C0201; PARTNO CL03A104MQ3NNNC
C31: 4700pF; C0201; PARTNO GRM033R71A472KA01D
L1, L2: 1uH; L2520P; PARTNO CIG22E1R0MNE
LED6: GRN; CHIPLED_0603; PARTNO QBLP601-AG
R18, R28: 27K; R0201; PARTNO RC0201JR-0727KL
R19, R26: 8.45K; R0201; PARTNO RC0603F8451CS
R21: 5.1; R0201; PARTNO RC0603J5R1CS
R25: 4.87K; R0201; PARTNO CRCW02014K87FKED
R29: 0.010; R0603; PARTNO RL0816T-R010-F
RP9: 2.2K; RP8_1506_1606; PARTNO MNR18E0APJ222
U5: LM26420XMHX/NOPB; MXA20A; PARTNO LM26420XMHX/NOPB
U6: INA210_DCK_6; DCK6; PARTNO INA210BIDCKR

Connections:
+1V2: +1V2.1, C33.1, R29.1, U6.5 (IN-); also elsewhere on the board
+3V3: C25.1, L1.1, R18.2; also elsewhere on the board
+5V: C27.1, C29.1, C30.1, R21.1, RP9.16 (2), U5.2 (EN1), U5.3 (VIND1), U5.4 (VIND1), U5.17 (VIND2), U5.18 (VIND2), U5.19 (EN2), U6.3 (V+); also elsewhere on the board
GND: C25.2, C27.2, C28.2, C29.2, C30.2, C31.2, C32.2, C33.2, LED6.C, R19.2, R26.1, U5.6 (PGND1), U5.7 (PGND1), U5.10 (DAP), U5.11 (DAP), U5.14 (PGND2), U5.15 (PGND2), U5.20 (AGND), U5.21 (DAP), U6.1 (REF), U6.2 (GND); also elsewhere on the board
HERCULES_ICORE: C31.1, R28.1; also elsewhere on the board
unnamed: L1.2, U5.5 (SW1)
unnamed: R18.1, R19.1, U5.8 (FB1)
unnamed: L2.1, U5.16 (SW2)
unnamed: C28.1, R21.2, U5.1 (VINC)
unnamed: R25.2, R26.2, U5.13 (FB2)
unnamed: C32.1, L2.2, R25.1, R29.2, U6.4 (IN+)
unnamed: R28.2, U6.6 (OUT)
RP12E: LED6.A, RP9.15 (1)

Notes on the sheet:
HERCULES POWER
POWER INDICATOR LED
+5V
